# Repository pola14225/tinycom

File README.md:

# TinyCom

A small and low cost modular computer system.

Features:
- dimensions less than 5x5cm
- single, dual or quad core 1GHz CPU
- 512GB or 1GB RAM
- USB, HDMI, WIFI, Bluetooth, SD-card, camera, microphones
- real-time clock with battery, on-board temperature sensor
- **made only from widely available parts**
- **can reliably be assembled at home with DIY tools**

Modules:
- TinyCom-A13
- [TinyCom-A20](#tinycom-a20)
- TinyCom-A64
- TinyCom-USB
- [TinyCom-HDMI](#tinycom-hdmi)
- TinyCom-Pilot

## TinyCom-A20

### Specifications

- Dimensions: 4x4 cm
- CPU: Allwinner A20 (Dual-Core ARM Cortex-A7 @ 1Ghz, 40nm process)
- Memory: 512MB DDR3 SDRAM
- PCB: 4 layers, 6 mil traces, 12 mil vias
- Ports: SD-card, serial, USBx3, HDMI, camera

### Pictures

## TinyCom-HDMI

- Connectors:  SD-card, USB, HDMI
- Network: WIFI, Bluetooth, ceramic antenna
- 2 microphones
- RTC backup battery
- Board temperature sensor
- PCB: 2 layers

### Pictures

## Contact

Send email to dj@netforce.com.

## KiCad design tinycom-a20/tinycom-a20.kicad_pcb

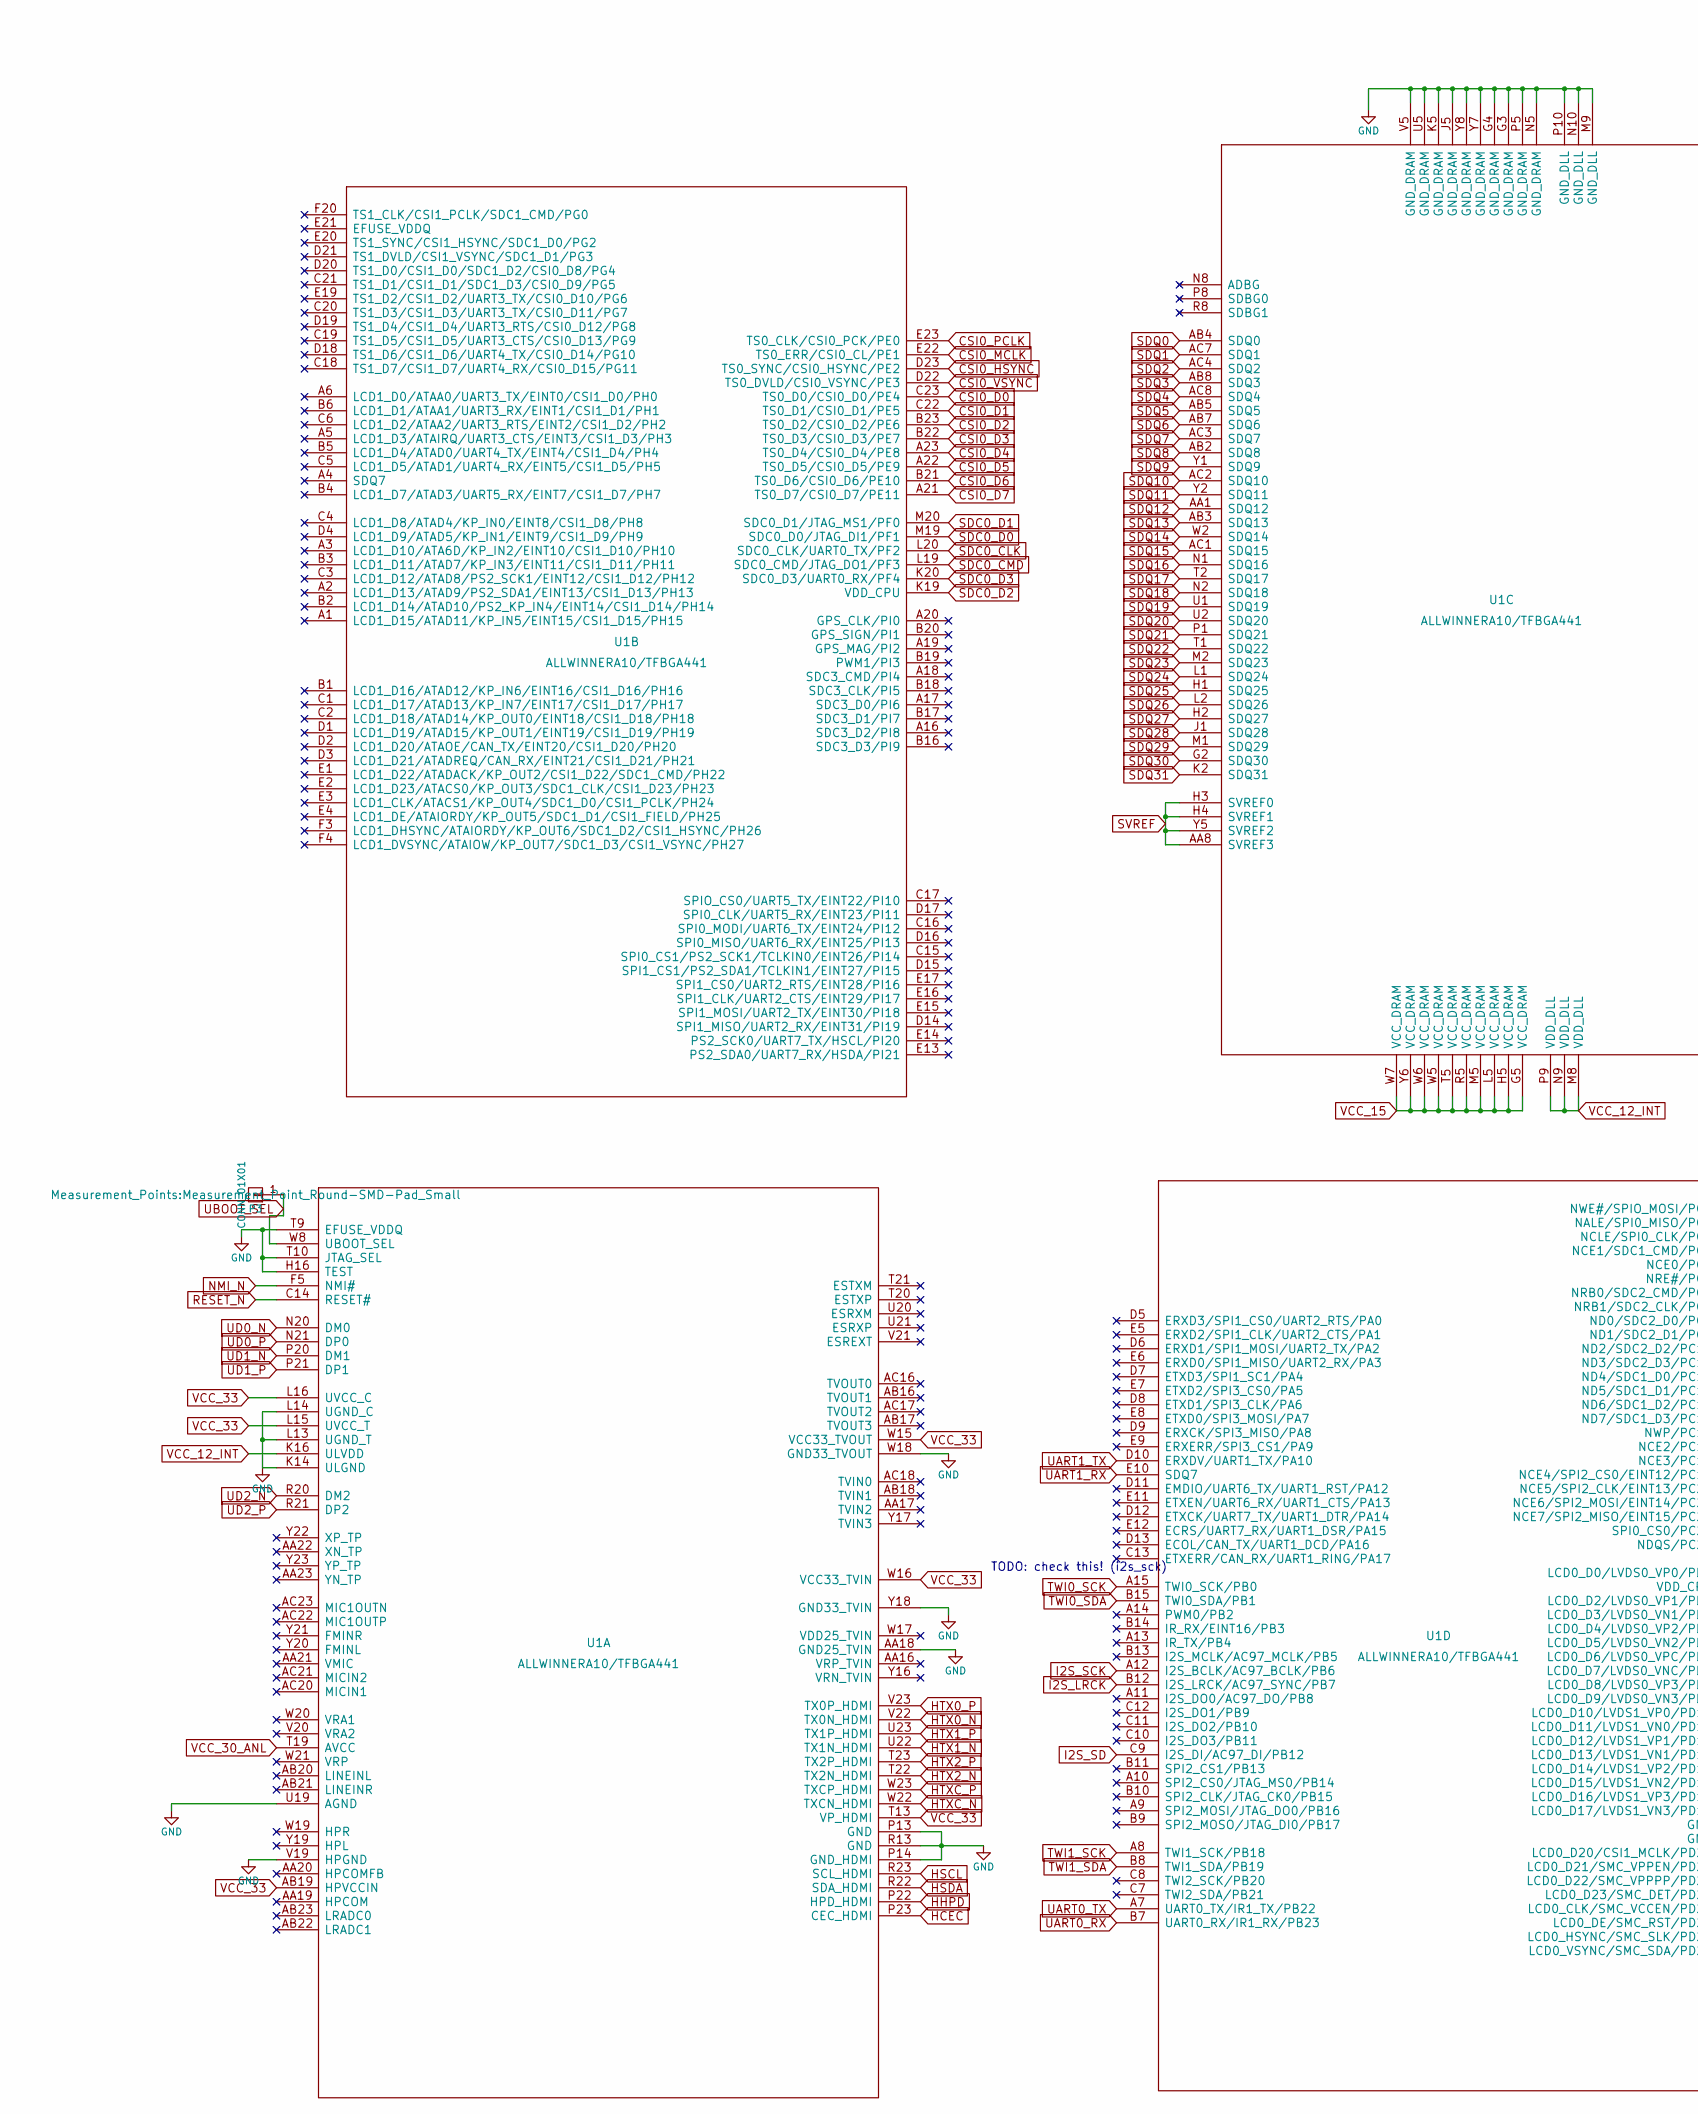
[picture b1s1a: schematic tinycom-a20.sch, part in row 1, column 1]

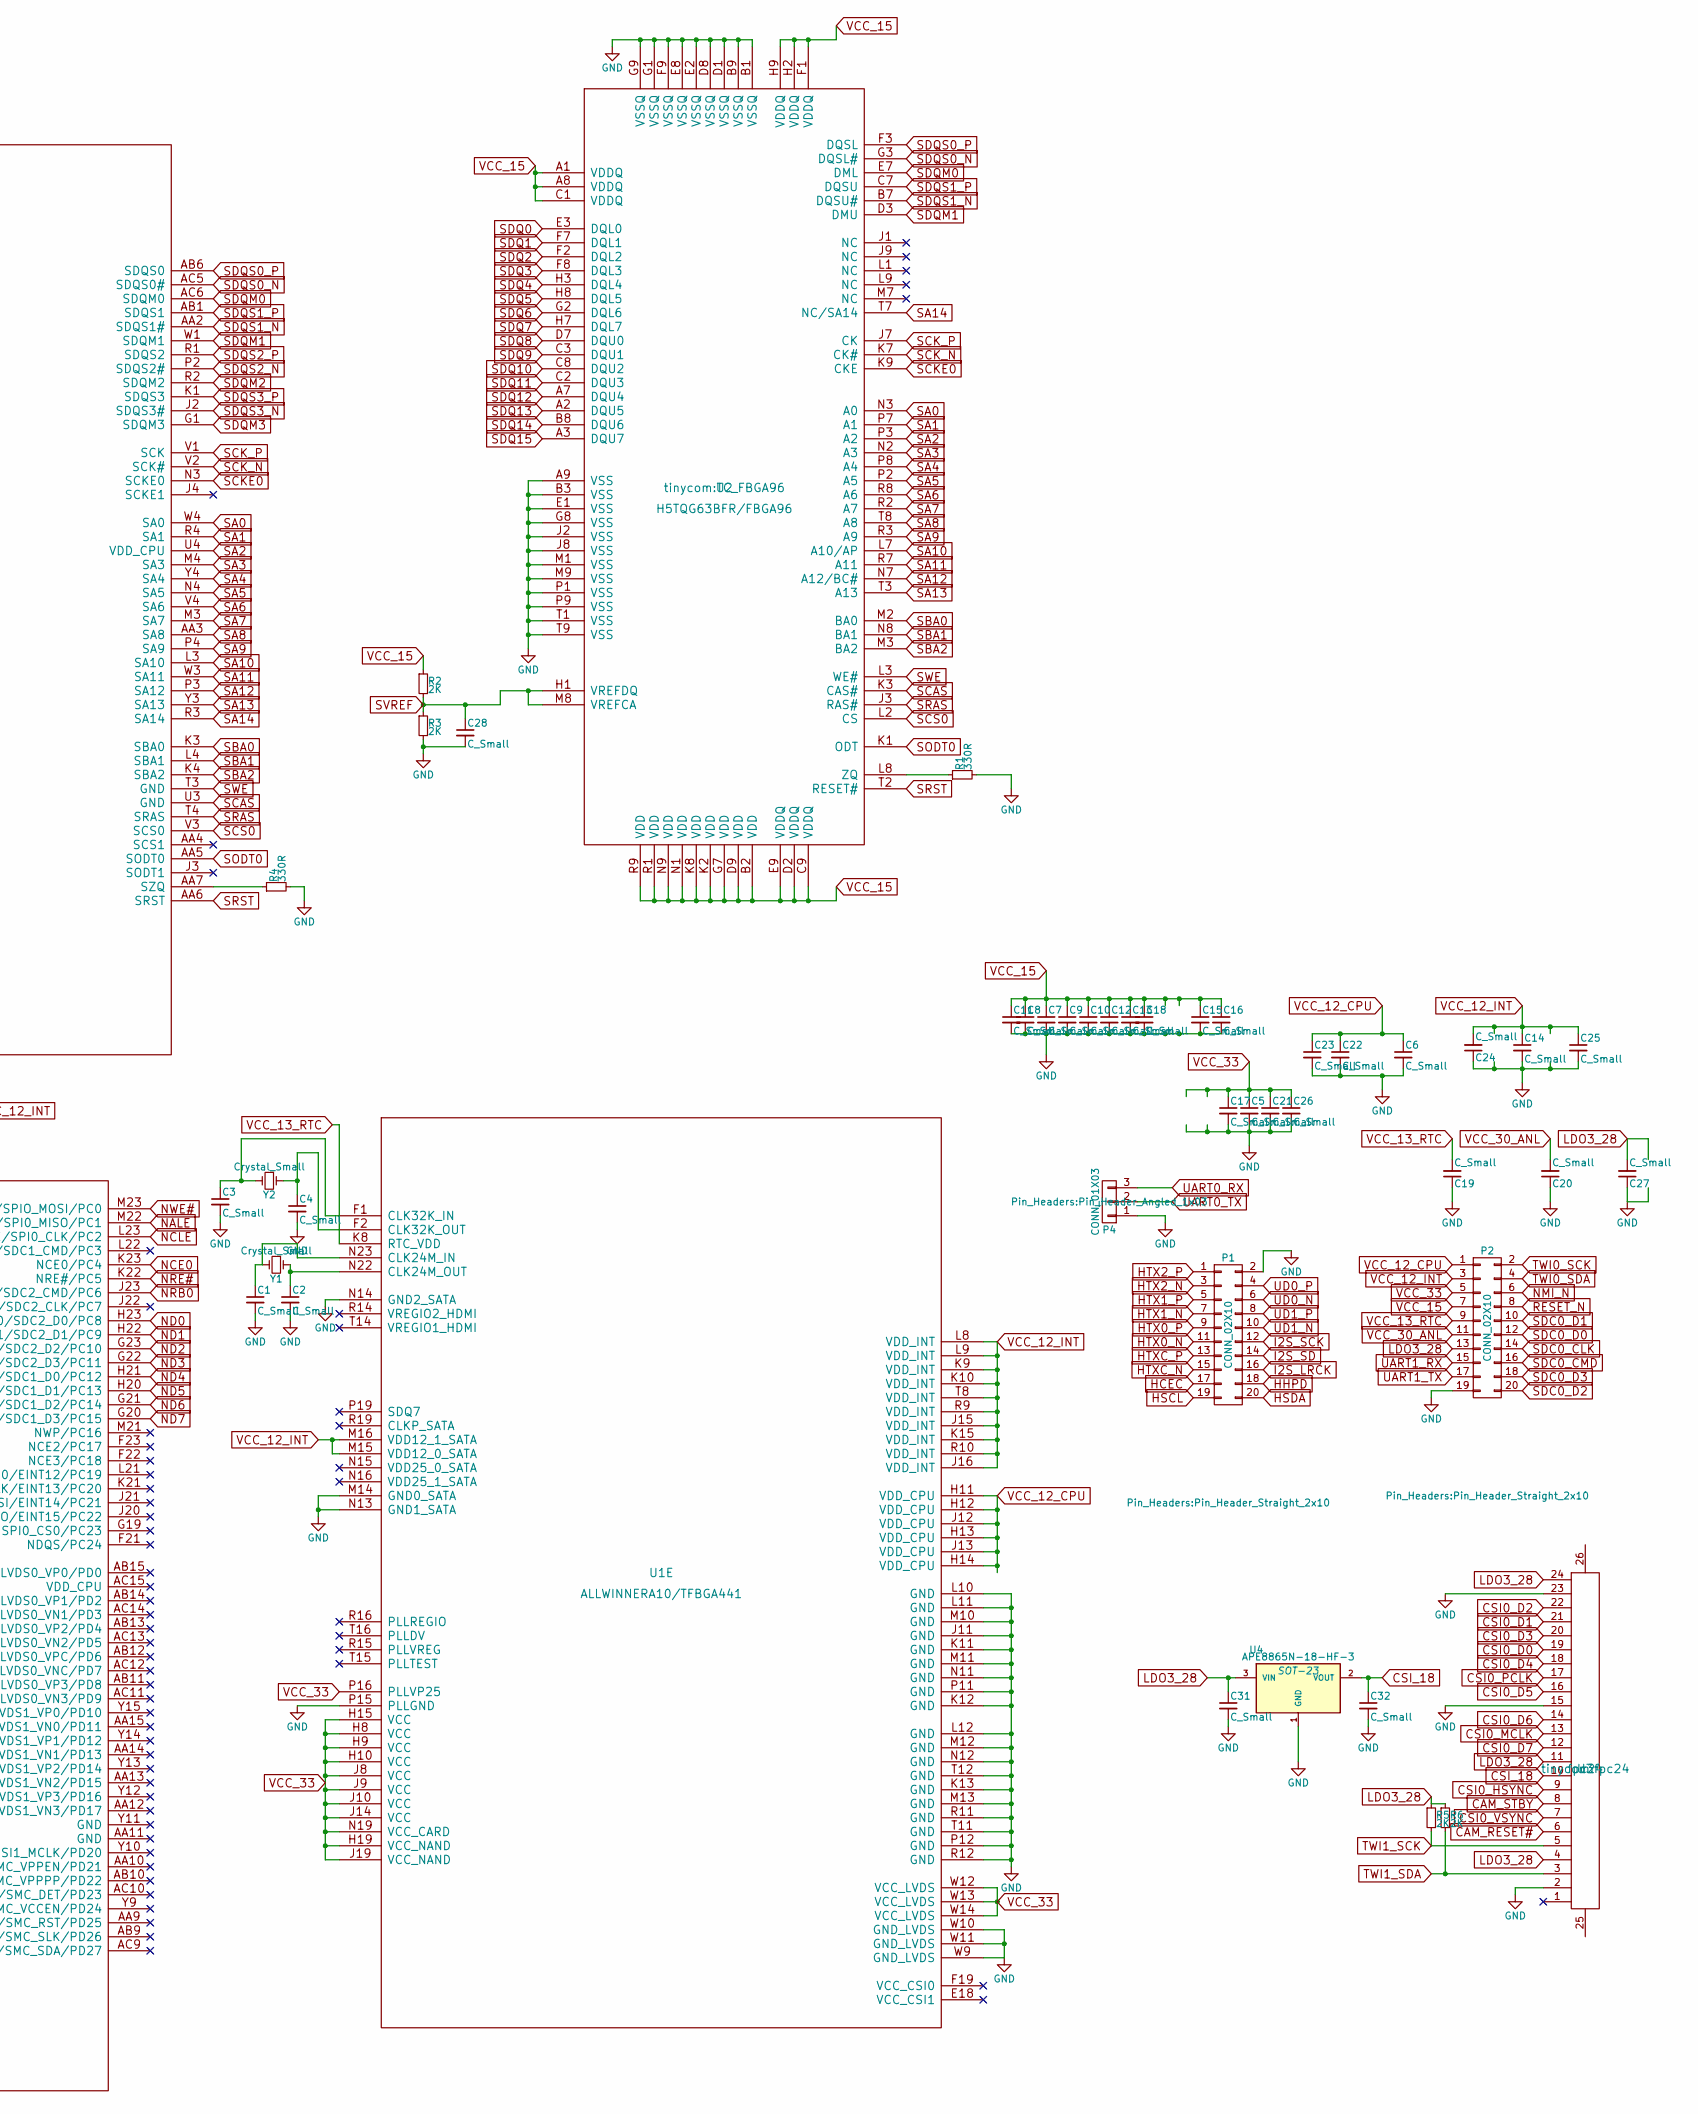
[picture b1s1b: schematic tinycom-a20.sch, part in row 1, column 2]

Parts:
C1, C2, C3, C4, C5, C6, C7, C8, C9, C10, C11, C12, C13, C14, C15, C16, C17, C18, C19, C20, C21, C22, C23, C24, C25, C26, C27, C28, C31, C32: C_Small; C_0603
P1, P2: CONN_02X10; Pin_Header_Straight_2x10
P3: CONN_01X01; Measurement_Point_Round-SMD-Pad_Small
P4: CONN_01X03; Pin_Header_Angled_1x03
R1, R4: 330R; R_0603
R2, R3, R5, R6: 2K; R_0603
U1: ALLWINNERA10/TFBGA441; 441TFBGA-P0.8
U2: H5TQG63BFR/FBGA96; TC_FBGA96
U3: fpc24
U4: APE8865N-18-HF-3; SOT-23
Y1: Crystal_Small; Crystal_5x3.2mm
Y2: Crystal_Small; crystal3215

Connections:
CAM_RESET#: U3.6
CAM_STBY: U3.8
CSI0_D0: U1.C23 (TS0_D0/CSI0_D0/PE4), U3.19
CSI0_D1: U1.C22 (TS0_D1/CSI0_D1/PE5), U3.21
CSI0_D2: U1.B23 (TS0_D2/CSI0_D2/PE6), U3.22
CSI0_D3: U1.B22 (TS0_D3/CSI0_D3/PE7), U3.20
CSI0_D4: U1.A23 (TS0_D4/CSI0_D4/PE8), U3.18
CSI0_D5: U1.A22 (TS0_D5/CSI0_D5/PE9), U3.16
CSI0_D6: U1.B21 (TS0_D6/CSI0_D6/PE10), U3.14
CSI0_D7: U1.A21 (TS0_D7/CSI0_D7/PE11), U3.12
CSI0_HSYNC: U1.D23 (TS0_SYNC/CSI0_HSYNC/PE2), U3.9
CSI0_MCLK: U1.E22 (TS0_ERR/CSI0_CL/PE1), U3.13
CSI0_PCLK: U1.E23 (TS0_CLK/CSI0_PCK/PE0), U3.17
CSI0_VSYNC: U1.D22 (TS0_DVLD/CSI0_VSYNC/PE3), U3.7
CSI_18: C32.1, U3.10, U4.2 (VOUT)
GND: C1.2, C2.2, C3.2, C4.2, C5.2, C6.2, C7.2, C8.2, C9.2, C10.2, C11.2, C12.2, C13.2, C14.2, C15.2, C16.2, C17.2, C18.2, C19.1, C20.1, C21.2, C22.2, C23.2, C24.1, C25.2, C26.2, C27.1, C28.2, C31.2, C32.2, P1.2, P2.19, P4.1, R1.2, R3.2, R4.2, U1.AA18 (GND25_TVIN), U1.G3 (GND_DRAM), U1.G4 (GND_DRAM), U1.H16 (TEST), U1.J5 (GND_DRAM), U1.J11 (GND), U1.K5 (GND_DRAM), U1.K11 (GND), U1.K12 (GND), U1.K13 (GND), U1.K14 (ULGND), U1.L10 (GND), U1.L11 (GND), U1.L12 (GND), U1.L13 (UGND_T), U1.L14 (UGND_C), U1.M9 (GND_DLL), U1.M10 (GND), U1.M11 (GND), U1.M12 (GND), U1.M13 (GND), U1.M14 (GND0_SATA), U1.N5 (GND_DRAM), U1.N10 (GND_DLL), U1.N11 (GND), U1.N12 (GND), U1.N13 (GND1_SATA), U1.N14 (GND2_SATA), U1.P5 (GND_DRAM), U1.P10 (GND_DLL), U1.P11 (GND), U1.P12 (GND), U1.P13 (GND), U1.P14 (GND_HDMI), U1.P15 (PLLGND), U1.R11 (GND), U1.R12 (GND), U1.R13 (GND), U1.T9 (EFUSE_VDDQ), U1.T10 (JTAG_SEL), U1.T11 (GND), U1.T12 (GND), U1.U5 (GND_DRAM), U1.U19 (AGND), U1.V5 (GND_DRAM), U1.V19 (HPGND), U1.W9 (GND_LVDS), U1.W10 (GND_LVDS), U1.W11 (GND_LVDS), U1.W18 (GND33_TVOUT), U1.Y7 (GND_DRAM), U1.Y8 (GND_DRAM), U1.Y18 (GND33_TVIN), U2.A9 (VSS), U2.B1 (VSSQ), U2.B3 (VSS), U2.B9 (VSSQ), U2.D1 (VSSQ), U2.D8 (VSSQ), U2.E1 (VSS), U2.E2 (VSSQ), U2.E8 (VSSQ), U2.F9 (VSSQ), U2.G1 (VSSQ), U2.G8 (VSS), U2.G9 (VSSQ), U2.J2 (VSS), U2.J8 (VSS), U2.M1 (VSS), U2.M9 (VSS), U2.P1 (VSS), U2.P9 (VSS), U2.T1 (VSS), U2.T9 (VSS), U3.2, U3.15, U3.23, U4.1 (GND)
HCEC: P1.17, U1.P23 (CEC_HDMI)
HHPD: P1.18, U1.P22 (HPD_HDMI)
HSCL: P1.19, U1.R23 (SCL_HDMI)
HSDA: P1.20, U1.R22 (SDA_HDMI)
HTX0_N: P1.11, U1.V22 (TX0N_HDMI)
HTX0_P: P1.9, U1.V23 (TX0P_HDMI)
HTX1_N: P1.7, U1.U22 (TX1N_HDMI)
HTX1_P: P1.5, U1.U23 (TX1P_HDMI)
HTX2_N: P1.3, U1.T22 (TX2N_HDMI)
HTX2_P: P1.1, U1.T23 (TX2P_HDMI)
HTXC_N: P1.15, U1.W22 (TXCN_HDMI)
HTXC_P: P1.13, U1.W23 (TXCP_HDMI)
I2S_LRCK: P1.16, U1.B12 (I2S_LRCK/AC97_SYNC/PB7)
I2S_SCK: P1.12, U1.A12 (I2S_BCLK/AC97_BCLK/PB6)
I2S_SD: P1.14, U1.C9 (I2S_DI/AC97_DI/PB12)
LDO3_28: C27.2, C31.1, P2.13, R5.1, R6.1, U3.4, U3.11, U3.24, U4.3 (VIN)
NALE: U1.M22 (NALE/SPI0_MISO/PC1)
NCE0: U1.K23 (NCE0/PC4)
NCLE: U1.L23 (NCLE/SPI0_CLK/PC2)
ND0: U1.H23 (ND0/SDC2_D0/PC8)
ND1: U1.H22 (ND1/SDC2_D1/PC9)
ND2: U1.G23 (ND2/SDC2_D2/PC10)
ND3: U1.G22 (ND3/SDC2_D3/PC11)
ND4: U1.H21 (ND4/SDC1_D0/PC12)
ND5: U1.H20 (ND5/SDC1_D1/PC13)
ND6: U1.G21 (ND6/SDC1_D2/PC14)
ND7: U1.G20 (ND7/SDC1_D3/PC15)
NMI_N: P2.6, U1.F5 (NMI#)
NRB0: U1.J23 (NRB0/SDC2_CMD/PC6)
NRE#: U1.K22 (NRE#/PC5)
NWE#: U1.M23 (NWE#/SPIO_MOSI/PC0)
unnamed: C1.1, U1.N23 (CLK24M_IN), Y1.2
unnamed: C2.1, U1.N22 (CLK24M_OUT), Y1.1
unnamed: C3.1, U1.F1 (CLK32K_IN), Y2.2
unnamed: C4.1, U1.F2 (CLK32K_OUT), Y2.1
unnamed: R1.1, U2.L8 (ZQ)
unnamed: R4.1, U1.AA7 (SZQ)
RESET_N: P2.8, U1.C14 (RESET#)
SA0: U1.W4 (SA0), U2.N3 (A0)
SA1: U1.R4 (SA1), U2.P7 (A1)
SA2: U1.U4 (VDD_CPU), U2.P3 (A2)
SA3: U1.M4 (SA3), U2.N2 (A3)
SA4: U1.Y4 (SA4), U2.P8 (A4)
SA5: U1.N4 (SA5), U2.P2 (A5)
SA6: U1.V4 (SA6), U2.R8 (A6)
SA7: U1.M3 (SA7), U2.R2 (A7)
SA8: U1.AA3 (SA8), U2.T8 (A8)
SA9: U1.P4 (SA9), U2.R3 (A9)
SA10: U1.L3 (SA10), U2.L7 (A10/AP)
SA11: U1.W3 (SA11), U2.R7 (A11)
SA12: U1.P3 (SA12), U2.N7 (A12/BC#)
SA13: U1.Y3 (SA13), U2.T3 (A13)
SA14: U1.R3 (SA14), U2.T7 (NC/SA14)
SBA0: U1.K3 (SBA0), U2.M2 (BA0)
SBA1: U1.L4 (SBA1), U2.N8 (BA1)
SBA2: U1.K4 (SBA2), U2.M3 (BA2)
SCAS: U1.U3 (GND), U2.K3 (CAS#)
SCKE0: U1.N3 (SCKE0), U2.K9 (CKE)
SCK_N: U1.V2 (SCK#), U2.K7 (CK#)
SCK_P: U1.V1 (SCK), U2.J7 (CK)
SCS0: U1.V3 (SCS0), U2.L2 (CS)
SDC0_CLK: P2.14, U1.L20 (SDC0_CLK/UART0_TX/PF2)
SDC0_CMD: P2.16, U1.L19 (SDC0_CMD/JTAG_DO1/PF3)
SDC0_D0: P2.12, U1.M19 (SDC0_D0/JTAG_DI1/PF1)
SDC0_D1: P2.10, U1.M20 (SDC0_D1/JTAG_MS1/PF0)
SDC0_D2: P2.20, U1.K19 (VDD_CPU)
SDC0_D3: P2.18, U1.K20 (SDC0_D3/UART0_RX/PF4)
SDQ0: U1.AB4 (SDQ0), U2.E3 (DQL0)
SDQ1: U1.AC7 (SDQ1), U2.F7 (DQL1)
SDQ2: U1.AC4 (SDQ2), U2.F2 (DQL2)
SDQ3: U1.AB8 (SDQ3), U2.F8 (DQL3)
SDQ4: U1.AC8 (SDQ4), U2.H3 (DQL4)
SDQ5: U1.AB5 (SDQ5), U2.H8 (DQL5)
SDQ6: U1.AB7 (SDQ6), U2.G2 (DQL6)
SDQ7: U1.AC3 (SDQ7), U2.H7 (DQL7)
SDQ8: U1.AB2 (SDQ8), U2.D7 (DQU0)
SDQ9: U1.Y1 (SDQ9), U2.C3 (DQU1)
SDQ10: U1.AC2 (SDQ10), U2.C8 (DQU2)
SDQ11: U1.Y2 (SDQ11), U2.C2 (DQU3)
SDQ12: U1.AA1 (SDQ12), U2.A7 (DQU4)
SDQ13: U1.AB3 (SDQ13), U2.A2 (DQU5)
SDQ14: U1.W2 (SDQ14), U2.B8 (DQU6)
SDQ15: U1.AC1 (SDQ15), U2.A3 (DQU7)
SDQ16: U1.N1 (SDQ16)
SDQ17: U1.T2 (SDQ17)
SDQ18: U1.N2 (SDQ18)
SDQ19: U1.U1 (SDQ19)
SDQ20: U1.U2 (SDQ20)
SDQ21: U1.P1 (SDQ21)
SDQ22: U1.T1 (SDQ22)
SDQ23: U1.M2 (SDQ23)
SDQ24: U1.L1 (SDQ24)
SDQ25: U1.H1 (SDQ25)
SDQ26: U1.L2 (SDQ26)
SDQ27: U1.H2 (SDQ27)
SDQ28: U1.J1 (SDQ28)
SDQ29: U1.M1 (SDQ29)
SDQ30: U1.G2 (SDQ30)
SDQ31: U1.K2 (SDQ31)
SDQM0: U1.AC6 (SDQM0), U2.E7 (DML)
SDQM1: U1.W1 (SDQM1), U2.D3 (DMU)
SDQM2: U1.R2 (SDQM2)
SDQM3: U1.G1 (SDQM3)
SDQS0_N: U1.AC5 (SDQS0#), U2.G3 (DQSL#)
SDQS0_P: U1.AB6 (SDQS0), U2.F3 (DQSL)
SDQS1_N: U1.AA2 (SDQS1#), U2.B7 (DQSU#)
SDQS1_P: U1.AB1 (SDQS1), U2.C7 (DQSU)
SDQS2_N: U1.P2 (SDQS2#)
SDQS2_P: U1.R1 (SDQS2)
SDQS3_N: U1.J2 (SDQS3#)
SDQS3_P: U1.K1 (SDQS3)
SODT0: U1.AA5 (SODT0), U2.K1 (ODT)
SRAS: U1.T4 (SRAS), U2.J3 (RAS#)
SRST: U1.AA6 (SRST), U2.T2 (RESET#)
SVREF: C28.1, R2.2, R3.1, U1.AA8 (SVREF3), U1.H3 (SVREF0), U1.H4 (SVREF1), U1.Y5 (SVREF2), U2.H1 (VREFDQ), U2.M8 (VREFCA)
SWE: U1.T3 (GND), U2.L3 (WE#)
TWI0_SCK: P2.2, U1.A15 (TWI0_SCK/PB0)
TWI0_SDA: P2.4, U1.B15 (TWI0_SDA/PB1)
TWI1_SCK: R5.2, U1.A8 (TWI1_SCK/PB18), U3.5
TWI1_SDA: R6.2, U1.B8 (TWI1_SDA/PB19), U3.3
UART0_RX: P4.3, U1.B7 (UART0_RX/IR1_RX/PB23)
UART0_TX: P4.2, U1.A7 (UART0_TX/IR1_TX/PB22)
UART1_RX: P2.15, U1.E10 (SDQ7)
UART1_TX: P2.17, U1.D10 (ERXDV/UART1_TX/PA10)
UBOOT_SEL: P3.1, U1.W8 (UBOOT_SEL)
UD0_N: P1.6, U1.N20 (DM0)
UD0_P: P1.4, U1.N21 (DP0)
UD1_N: P1.10, U1.P20 (DM1)
UD1_P: P1.8, U1.P21 (DP1)
UD2_N: U1.R20 (DM2)
UD2_P: U1.R21 (DP2)
VCC_12_CPU: C6.1, C22.1, C23.1, P2.1, U1.H11 (VDD_CPU), U1.H12 (VDD_CPU), U1.H13 (VDD_CPU), U1.H14 (VDD_CPU), U1.J12 (VDD_CPU), U1.J13 (VDD_CPU)
VCC_12_INT: C14.1, C24.2, C25.1, P2.3, U1.J15 (VDD_INT), U1.J16 (VDD_INT), U1.K9 (VDD_INT), U1.K10 (VDD_INT), U1.K15 (VDD_INT), U1.K16 (ULVDD), U1.L8 (VDD_INT), U1.L9 (VDD_INT), U1.M8 (VDD_DLL), U1.M15 (VDD12_0_SATA), U1.M16 (VDD12_1_SATA), U1.N9 (VDD_DLL), U1.P9 (VDD_DLL), U1.R9 (VDD_INT), U1.R10 (VDD_INT), U1.T8 (VDD_INT)
VCC_13_RTC: C19.2, P2.9, U1.K8 (RTC_VDD)
VCC_15: C7.1, C8.1, C9.1, C10.1, C11.1, C12.1, C13.1, C15.1, C16.1, C18.1, P2.7, R2.1, U1.G5 (VCC_DRAM), U1.H5 (VCC_DRAM), U1.L5 (VCC_DRAM), U1.M5 (VCC_DRAM), U1.R5 (VCC_DRAM), U1.T5 (VCC_DRAM), U1.W5 (VCC_DRAM), U1.W6 (VCC_DRAM), U1.W7 (VCC_DRAM), U1.Y6 (VCC_DRAM), U2.A1 (VDDQ), U2.A8 (VDDQ), U2.B2 (VDD), U2.C1 (VDDQ), U2.C9 (VDDQ), U2.D2 (VDDQ), U2.D9 (VDD), U2.E9 (VDDQ), U2.F1 (VDDQ), U2.G7 (VDD), U2.H2 (VDDQ), U2.H9 (VDDQ), U2.K2 (VDD), U2.K8 (VDD), U2.N1 (VDD), U2.N9 (VDD), U2.R1 (VDD), U2.R9 (VDD)
VCC_30_ANL: C20.2, P2.11, U1.T19 (AVCC)
VCC_33: C5.1, C17.1, C21.1, C26.1, P2.5, U1.AB19 (HPVCCIN), U1.H8 (VCC), U1.H9 (VCC), U1.H10 (VCC), U1.H15 (VCC), U1.H19 (VCC_NAND), U1.J8 (VCC), U1.J9 (VCC), U1.J10 (VCC), U1.J14 (VCC), U1.J19 (VCC_NAND), U1.L15 (UVCC_T), U1.L16 (UVCC_C), U1.N19 (VCC_CARD), U1.P16 (PLLVP25), U1.T13 (VP_HDMI), U1.W12 (VCC_LVDS), U1.W13 (VCC_LVDS), U1.W14 (VCC_LVDS), U1.W15 (VCC33_TVOUT), U1.W16 (VCC33_TVIN)

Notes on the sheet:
TODO: check this! (i2s_sck)

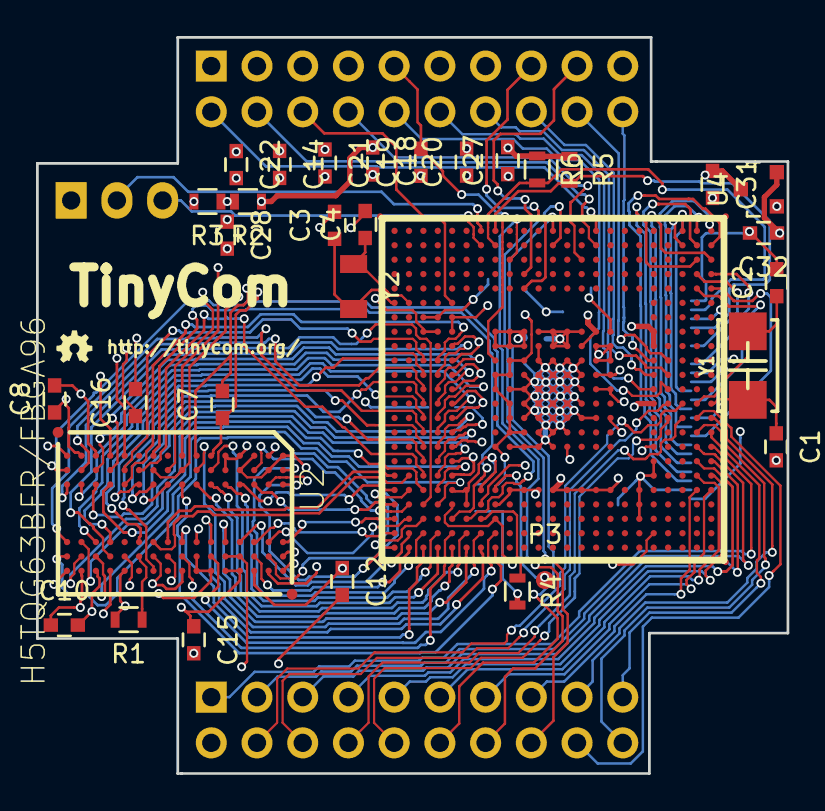
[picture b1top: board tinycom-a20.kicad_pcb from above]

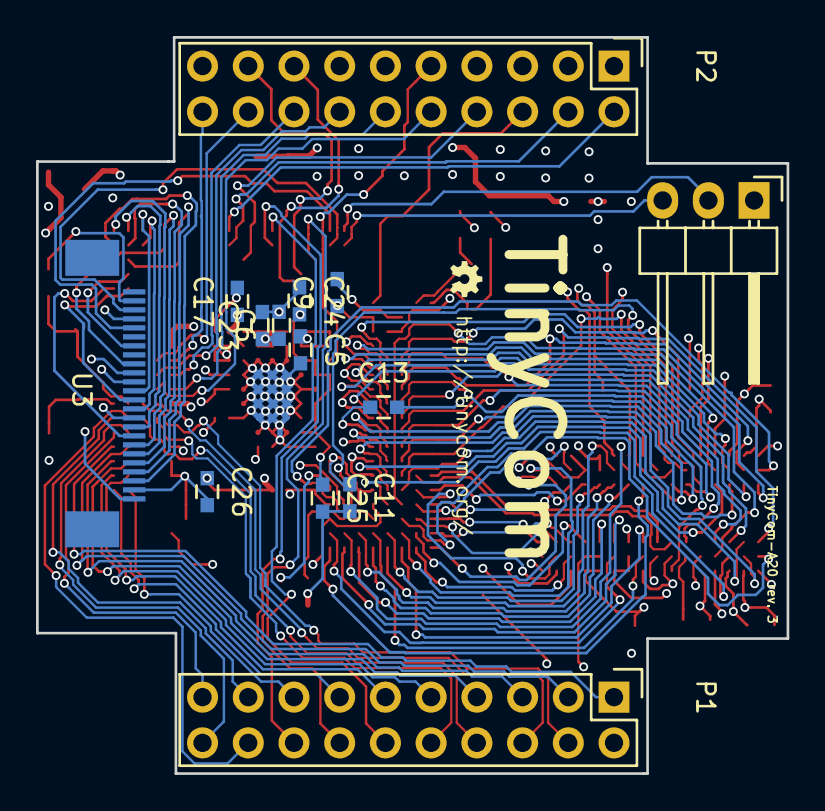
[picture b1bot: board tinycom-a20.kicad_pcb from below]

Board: 4 copper layers, 41.7 x 40.9 mm, 46 parts (14 on the bottom side), 113 nets.

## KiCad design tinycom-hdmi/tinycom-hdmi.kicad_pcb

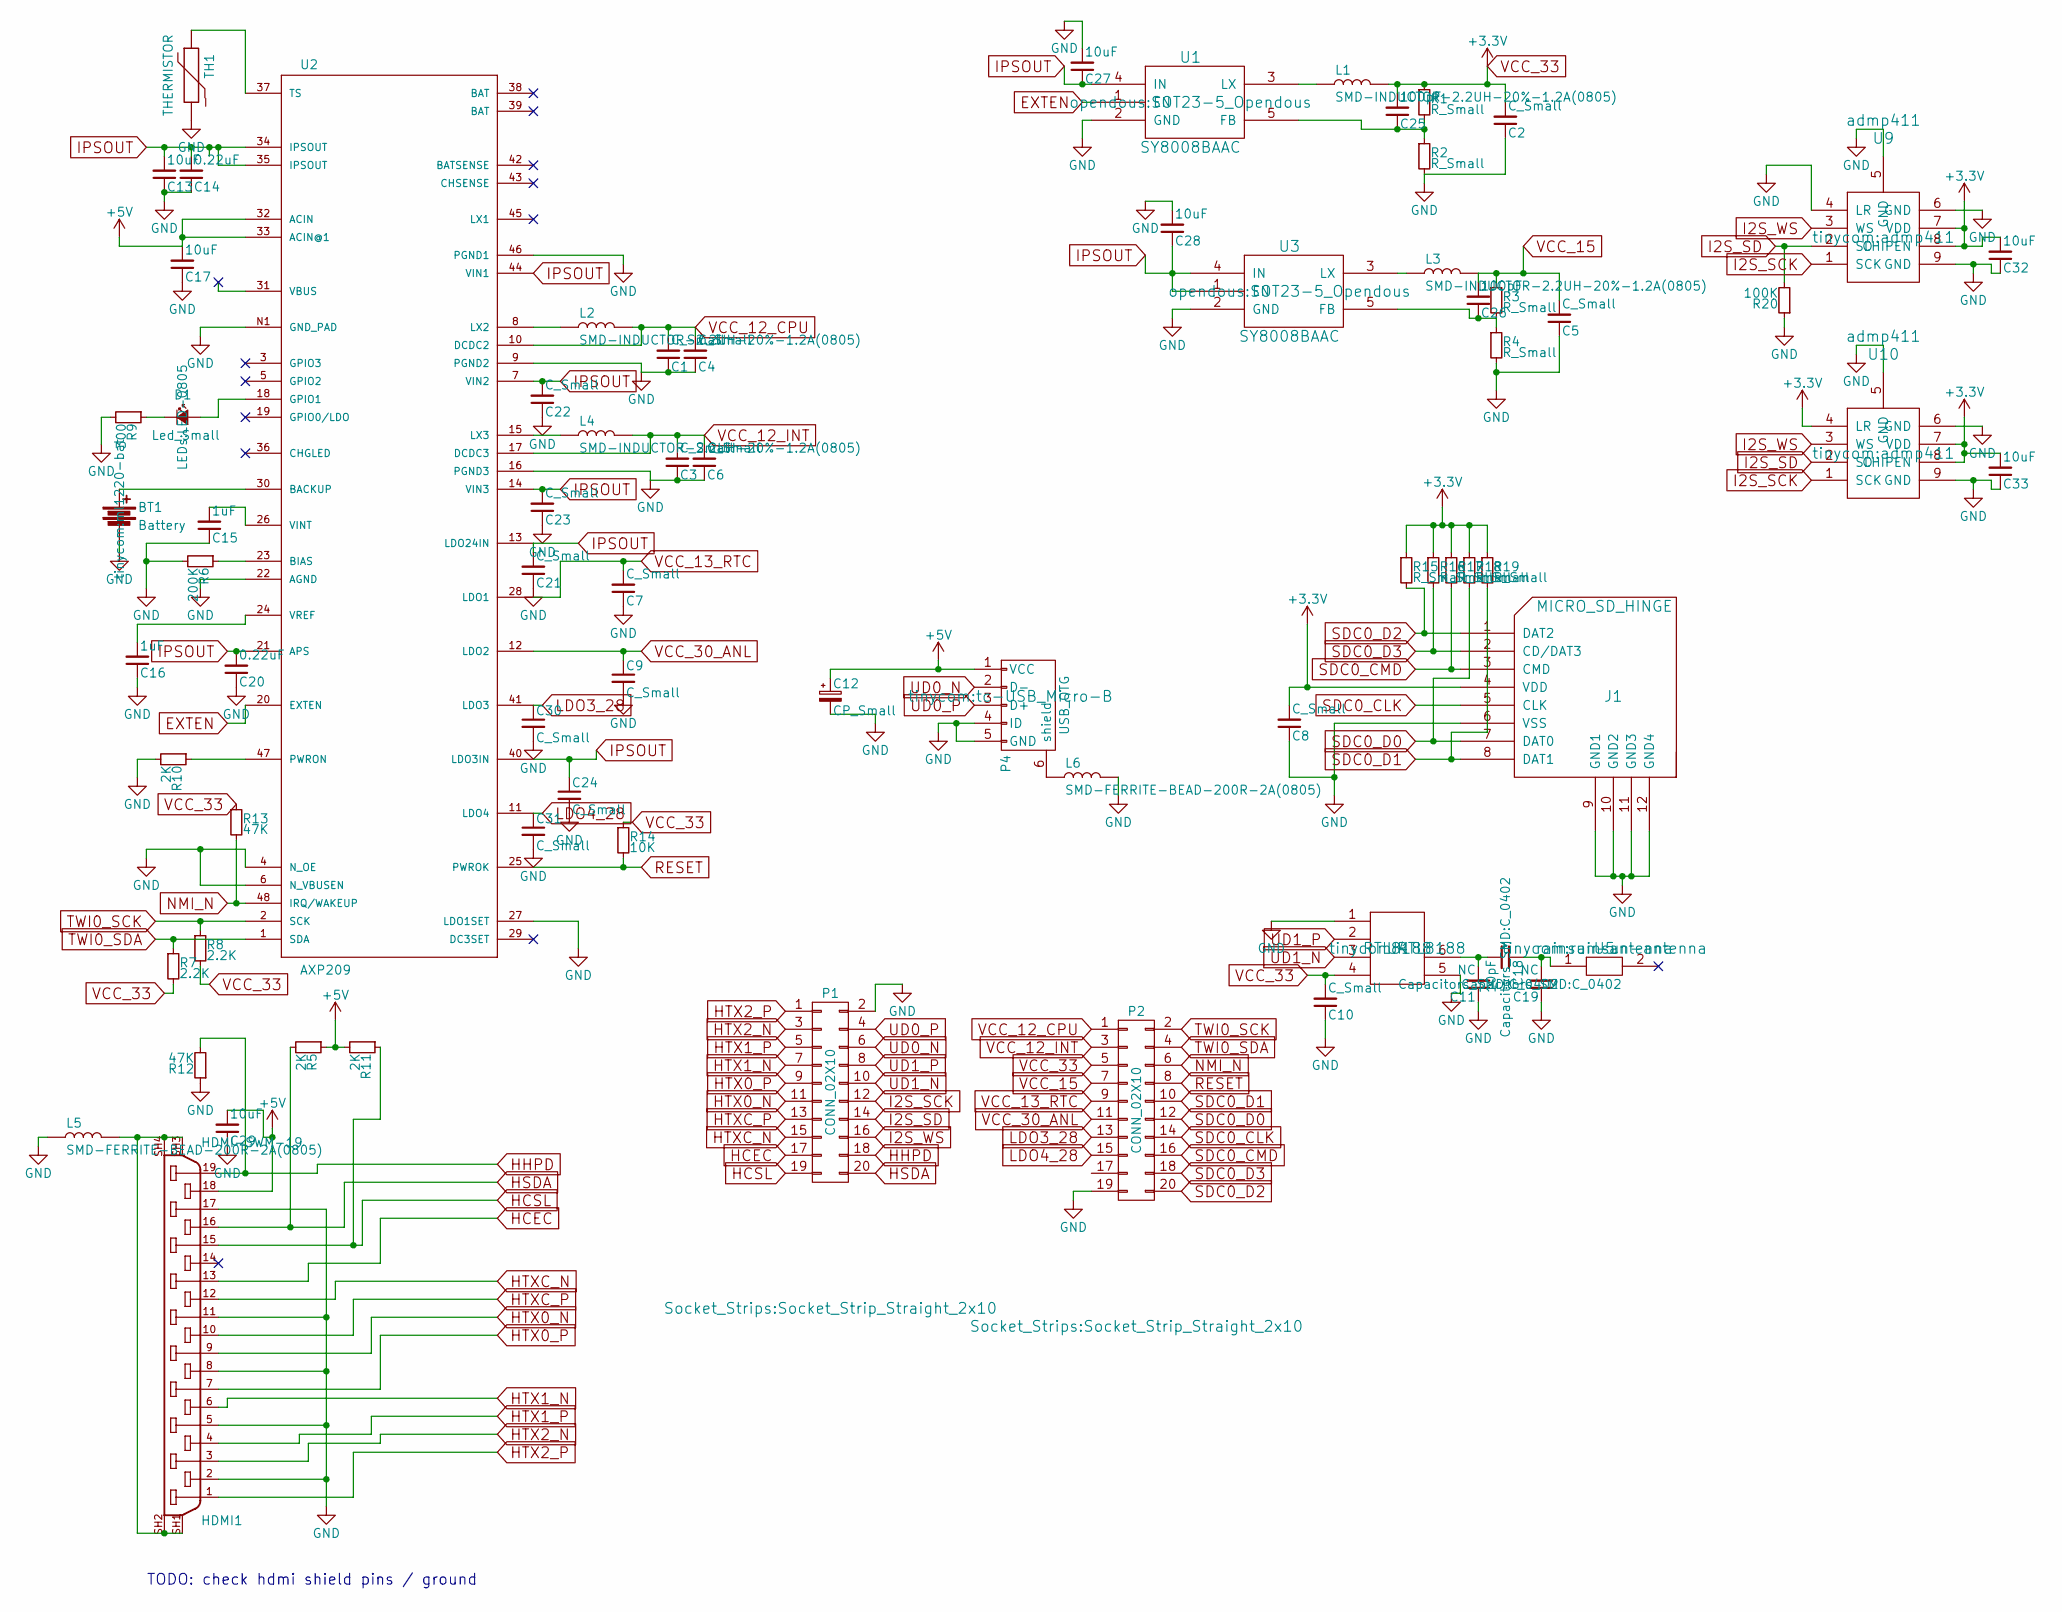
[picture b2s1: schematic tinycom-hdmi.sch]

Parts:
BT1: Battery; ml1220-bat
C1, C2, C3, C5, C21, C22, C23: C_Small; C_1206
C4, C6, C7, C8, C9, C10, C24, C30, C31: C_Small; C_0805
C11, C19: NC; C_0402
C12: CP_Small; TantalC_SizeA_EIA-3216_Reflow
C13, C17, C32, C33: 10uF; C_0805
C14, C20: 0.22uF; C_0805
C15, C16: 1uF; C_0805
C18: 10pF; C_0402
C25, C26: 100pF; C_1206
C27, C28, C29: 10uF; C_1206
D1: Led_Small; LED-0805
HDMI1: HDMI-SWM-19
J1: MICRO_SD_HINGE; MICRO_SD_HINGE_AMP
L1, L2, L3, L4: SMD-INDUCTOR-2.2UH-20%-1.2A(0805); CD32
L5, L6: SMD-FERRITE-BEAD-200R-2A(0805); OPL-Inductor-L0805
P1, P2: CONN_02X10; Socket_Strip_Straight_2x10
P4: USB_OTG; tc-USB_Micro-B
R1, R2, R3, R4, R15, R16, R17, R18, R19: R_Small; R_0805
R5, R10, R11: 2K; R_0805
R6: 200K; R_0805
R7, R8: 2.2K; R_0805
R9: 300; R_0805
R12, R13: 47K; R_0805
R14: 10K; R_0805
R20: 100K; R_0805
TH1: THERMISTOR; R1
U1, U3: SY8008BAAC; SOT23-5_Opendous
U2: AXP209; ax209
U4: RTL8188
U5: rainsun-antenna
U9, U10: admp411

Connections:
+5V: C12.1, C17.2, C29.2, HDMI1.18, P4.1 (VCC), R5.1, R11.2, U2.32 (ACIN), U2.33 (ACIN@1)
EXTEN: U1.1 (EN), U2.20 (EXTEN)
GND: BT1.2, C1.1, C2.1, C3.1, C4.1, C5.1, C6.1, C7.1, C8.1, C9.2, C10.1, C11.1, C12.2, C13.1, C14.1, C15.1, C16.1, C17.1, C19.1, C20.1, C21.1, C22.1, C23.1, C24.2, C27.2, C28.2, C29.1, C30.2, C31.2, C32.1, C33.1, HDMI1.2, HDMI1.5, HDMI1.8, HDMI1.11, HDMI1.17, J1.6 (VSS), J1.9 (GND1), J1.10 (GND2), J1.11 (GND3), J1.12 (GND4), L5.1, L6.2, P1.2, P2.19, P4.4 (ID), P4.5 (GND), R2.2, R4.2, R6.2, R9.2, R10.2, R12.1, R20.1, TH1.2, U1.2 (GND), U2.4 (N_OE), U2.6 (N_VBUSEN), U2.9 (PGND2), U2.16 (PGND3), U2.22 (AGND), U2.27 (LDO1SET), U2.46 (PGND1), U2.N1 (GND_PAD), U3.2 (GND), U4.1, U4.5, U9.4 (LR), U9.5 (GND), U9.6 (GND), U9.9 (GND), U10.5 (GND), U10.6 (GND), U10.9 (GND)
HCEC: HDMI1.13, P1.17
HCSL: HDMI1.15, P1.19, R11.1
HHPD: HDMI1.19, P1.18, R12.2
HSDA: HDMI1.16, P1.20, R5.2
HTX0_N: HDMI1.9, P1.11
HTX0_P: HDMI1.7, P1.9
HTX1_N: HDMI1.6, P1.7
HTX1_P: HDMI1.4, P1.5
HTX2_N: HDMI1.3, P1.3
HTX2_P: HDMI1.1, P1.1
HTXC_N: HDMI1.12, P1.15
HTXC_P: HDMI1.10, P1.13
I2S_SCK: P1.12, U9.1 (SCK), U10.1 (SCK)
I2S_SD: P1.14, R20.2, U9.2 (SD), U10.2 (SD)
I2S_WS: P1.16, U9.3 (WS), U10.3 (WS)
IPSOUT: C13.2, C14.2, C20.2, C21.2, C22.2, C23.2, C24.1, C27.1, C28.1, U1.4 (IN), U2.7 (VIN2), U2.13 (LDO24IN), U2.14 (VIN3), U2.21 (APS), U2.34 (IPSOUT), U2.35 (IPSOUT), U2.40 (LDO3IN), U2.44 (VIN1), U3.1 (EN), U3.4 (IN)
LDO3_28: C30.1, P2.13, U2.41 (LDO3)
LDO4_28: C31.1, P2.15, U2.11 (LDO4)
NMI_N: P2.6, R13.2, U2.48 (IRQ/WAKEUP)
unnamed: BT1.1, U2.30 (BACKUP)
unnamed: C11.2, C18.2, U4.6
unnamed: C15.2, U2.26 (VINT)
unnamed: C16.2, U2.24 (VREF)
unnamed: C18.1, C19.2, U5.1
unnamed: C25.1, R1.2, R2.1, U1.5 (FB)
unnamed: C26.1, R3.2, R4.1, U3.5 (FB)
unnamed: D1.1 (K), R9.1
unnamed: D1.2 (A), U2.18 (GPIO1)
unnamed: HDMI1.SH1 (20), HDMI1.SH2 (21), HDMI1.SH3 (22), HDMI1.SH4 (23), L5.2
unnamed: L1.1, U1.3 (LX)
unnamed: L2.1, U2.8 (LX2)
unnamed: L3.1, U3.3 (LX)
unnamed: L4.1, U2.15 (LX3)
unnamed: L6.1, P4.6 (shield)
unnamed: R6.1, U2.23 (BIAS)
unnamed: R10.1, U2.47 (PWRON)
unnamed: TH1.1, U2.37 (TS)
RESET: P2.8, R14.2, U2.25 (PWROK)
SDC0_CLK: J1.5 (CLK), P2.14
SDC0_CMD: J1.3 (CMD), P2.16, R17.2
SDC0_D0: J1.7 (DAT0), P2.12, R18.2
SDC0_D1: J1.8 (DAT1), P2.10, R19.2
SDC0_D2: J1.1 (DAT2), P2.20, R15.2
SDC0_D3: J1.2 (CD/DAT3), P2.18, R16.2
TWI0_SCK: P2.2, R8.1, U2.2 (SCK)
TWI0_SDA: P2.4, R7.1, U2.1 (SDA)
UD0_N: P1.6, P4.2 (D-)
UD0_P: P1.4, P4.3 (D+)
UD1_N: P1.10, U4.3
UD1_P: P1.8, U4.2
VCC_12_CPU: C1.2, C4.2, L2.2, P2.1, U2.10 (DCDC2)
VCC_12_INT: C3.2, C6.2, L4.2, P2.3, U2.17 (DCDC3)
VCC_13_RTC: C7.2, P2.9, U2.28 (LDO1)
VCC_15: C5.2, C26.2, L3.2, P2.7, R3.1
VCC_30_ANL: C9.1, P2.11, U2.12 (LDO2)
VCC_33: C2.2, C8.2, C10.2, C25.2, C32.2, C33.2, J1.4 (VDD), L1.2, P2.5, R1.1, R7.2, R8.2, R13.1, R14.1, R15.1, R16.1, R17.1, R18.1, R19.1, U4.4, U9.7 (VDD), U9.8 (CHIPEN), U10.4 (LR), U10.7 (VDD), U10.8 (CHIPEN)

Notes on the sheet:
TODO: check hdmi shield pins / ground

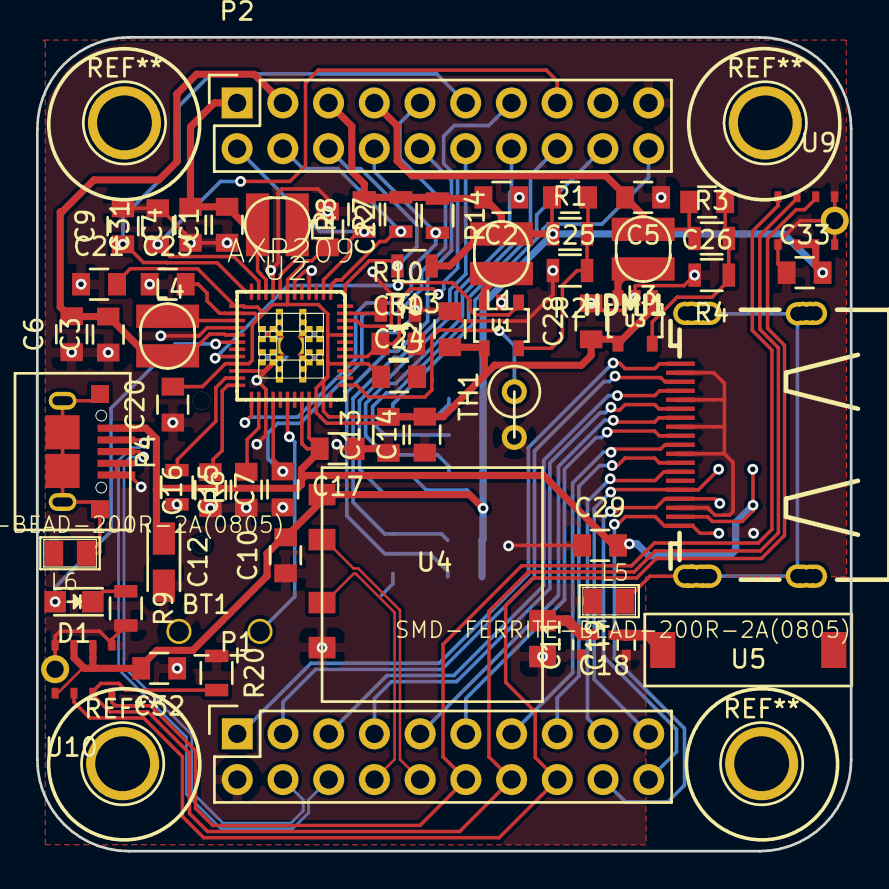
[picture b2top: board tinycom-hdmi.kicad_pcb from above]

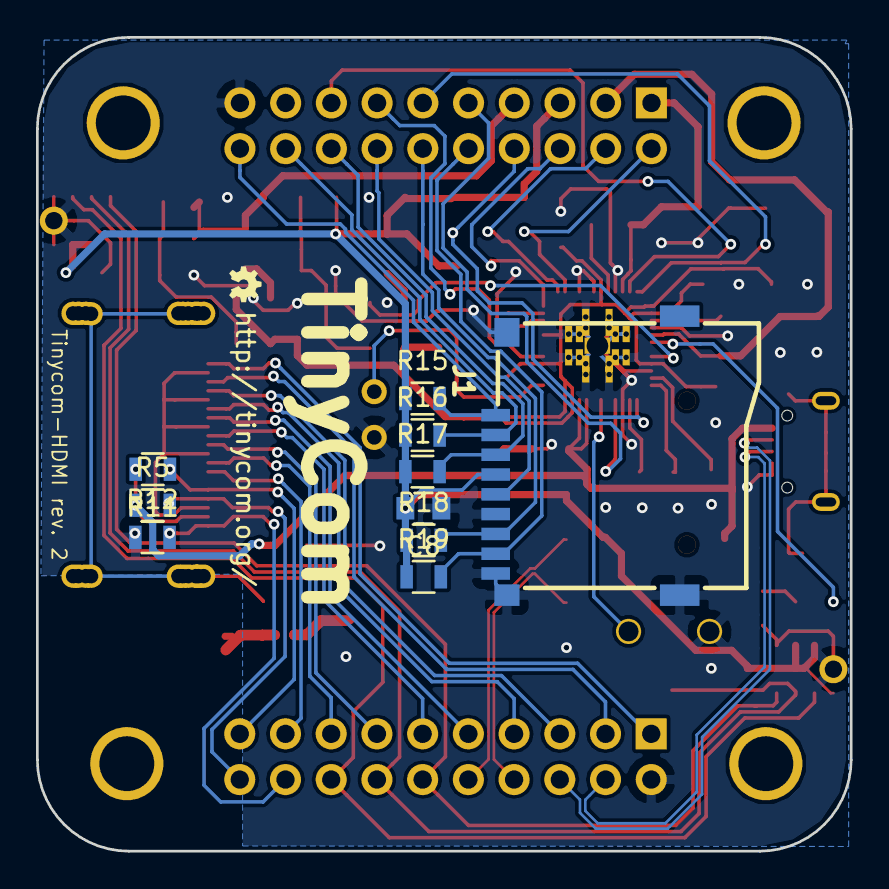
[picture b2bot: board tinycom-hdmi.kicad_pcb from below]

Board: 2 copper layers, 45.2 x 45.2 mm, 74 parts (10 on the bottom side), 59 nets.
